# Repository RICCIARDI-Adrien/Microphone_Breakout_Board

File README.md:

# Microphone breakout board

A simple breakout board for the Knowles SPW0878LR5H-1 Ellen analog microphone.

## PCB production files generation

Use the `Makefile` located in the `Hardware` directory to panelize the board or to generate the production files.

## Photo gallery

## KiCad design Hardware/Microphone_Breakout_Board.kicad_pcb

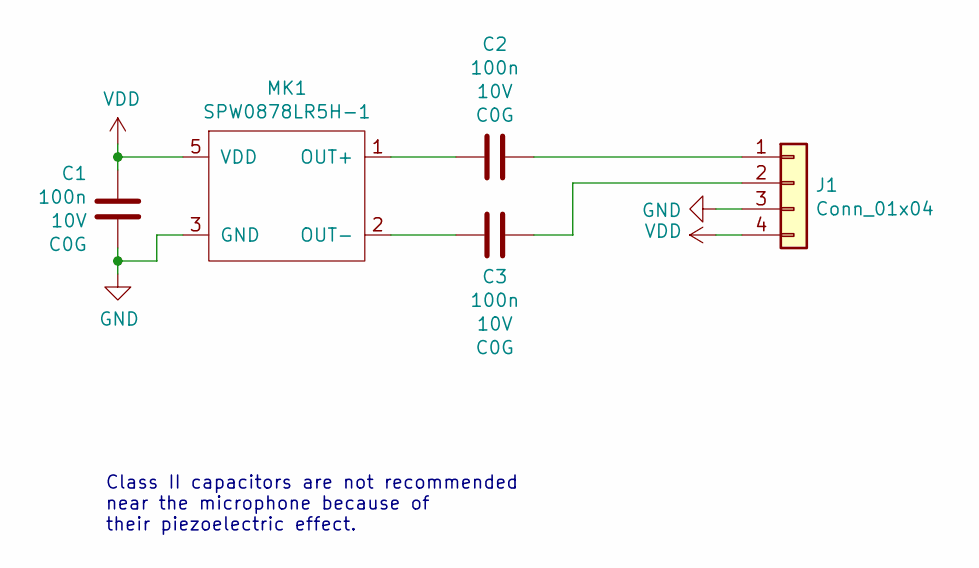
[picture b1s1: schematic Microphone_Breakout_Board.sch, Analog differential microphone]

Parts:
C1, C2, C3: 100n; C_1206_3216Metric; PartNumber C3216C0G1H104J160AA
J1: Conn_01x04; PinHeader_1x04_P2.54mm_Horizontal; PartNumber 10129379-904002BLF
MK1: SPW0878LR5H-1; PartNumber SPW0878LR5H-1

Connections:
GND: C1.2, J1.3, MK1.3 (GND), MK1.4 (GND)
unnamed: C2.1, J1.1
unnamed: C2.2, MK1.1 (OUT+)
unnamed: C3.1, J1.2
unnamed: C3.2, MK1.2 (OUT-)
VDD: C1.1, J1.4, MK1.5 (VDD)

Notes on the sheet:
Class II capacitors are not recommended near the microphone because of their piezoelectric effect.

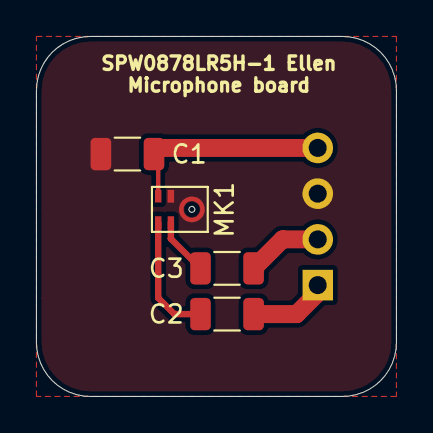
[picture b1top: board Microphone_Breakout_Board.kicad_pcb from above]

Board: 2 copper layers, 20.0 x 20.0 mm, 5 parts (1 on the bottom side), 6 nets.

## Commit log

2022-02-09 Initial commit. Started board schematic, added microphone symbol.
2022-02-09 Added microphone footprint.
2022-02-09 Added circuit schematic.
2022-02-11 Routed PCB.
2022-02-11 Added manufacturing data to schematic and PCB.
2022-02-14 Added automated panelization support.
2022-02-14 Added automated production and assembly files generation. Modified the schematic and the PCB accordingly to provide the correct parameters to KiKit.
2022-02-14 Added JLC PCB compatible production files generation.
2022-02-14 Added README.md.
2022-04-02 Added assembled board pictures to README.md.
2022-04-02 Added MIT license.
